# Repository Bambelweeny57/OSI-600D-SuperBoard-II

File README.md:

# Ohio Scientific (OSI) 600D Superboard II Recreation

An open-source hardware recreation of the **Ohio Scientific Superboard II, Model 600 revision D**, the classic 6502 single-board computer, as a complete **KiCad 10** project.

The board keeps the original circuit and copper layout, and adds **Cherry MX keyswitches**, ROM sockets for modern **27C16 EPROMs or 2816 EEPROMs**, pin headers for the option jumpers and a fused power input.

As far as we know, this is the first native KiCad PCB and schematic of the 600D, and the only electronic version of its schematic apart from the original scans.

## Project status

- [x] **Gerber import:** layout converted into KiCad 10 from the reproduction Gerber files by Grant (Klyball).
- [x] **Native KiCad board:** imported copper cleaned up into tracks, vias and footprints; via rings, thin tracks and track ends tidied; mounting holes converted to footprints.
- [x] **Schematic:** five hierarchical sheets following the five OSI pages, with logic drawn as gates. The schematic netlist matches the PCB exactly (269 nets).
- [x] **Verification:** every net checked against the OSI 600 rev D schematic (28 Aug 1980, sheets 1–5), and nets named after the original signal names.
- [x] **DRC:** no violations and no unconnected pads, with the default clearance set to 0.15 mm (the original artwork's spacing).
- [x] **Documentation:** schematic and layout booklet, assembly and test guide, interactive BOM.
- [x] **Schematic wiring:** sheets currently connect by net labels; drawing the wires to match the original pages is in progress.
- [x] **3D model:** Cherry MX switch and keycap models for the 3D view.
- [ ] **First build:** prototype boards to be ordered and tested.

## Repository layout

| Folder | Contents |
|---|---|
| `src/` | KiCad 10 project: top-level schematic, the five sheet files and the PCB |
| `documents/` | Schematic and layout booklet (PDF) and the assembly and test guide (Word) |
| `bom/` | Interactive BOM (`ibom.html`) |
| `images/` | Renders and images used in this README |
| `models/` | 3D models for the KiCad 3D viewer |

## The hardware

| | |
|---|---|
| CPU | MOS 6502 at about 1 MHz (3.93216 MHz crystal) |
| RAM | 8 KB on board in 2114 chips (the original shipped with 4 KB fitted) |
| ROM | Monitor (SYN600) at $F800 and 8 KB Microsoft BASIC at $A000–$BFFF |
| Video | Composite monochrome output, 1 KB video RAM, 2716-type character generator; 32/64 character mode select |
| Keyboard | 53 keys plus Break in the original OSI layout, using Cherry MX switches |
| Storage | Cassette interface; RS-232 serial option through the 6850 ACIA |
| Sound | 8-bit DAC output on J4 |
| Expansion | 40-pin J1 for an OSI 610 board; J75 for the colour option |

## What changed from the original board

- **Cherry MX keyboard:** 54 switch positions. The shift lock can be a Cherry MX Lock switch at SW38 (the original position) or a latching switch at SW54; fit only one.
- **ROMs:** the monitor (U13) and BASIC (U9–U12) sockets take 27C16 or 2816 parts. The character generator (U41) is a 2716-type EPROM.
- **Jumpers:** the original wire-jumper blocks are replaced by pin headers W3 and W5.
- **Power:** 5 V enters at the `+5V_IN` holes and passes through fuse F1 before the protection diode D15.
- **Break key (SW40):** snip off the right-hand plastic peg of the switch; that hole was removed because it cut into the ground strip.
- **Do not fit R88.**

### Reference designators changed for KiCad

KiCad needs every reference to be unique and to end in a number, so these parts were renumbered:

| On the OSI sheets | On this board | Part |
|---|---|---|
| R74 (sheet 1) | R88 | 390 Ω DD pull-down, not fitted |
| R62A (sheet 3) | R90 | 100 Ω cassette input resistor |
| R86 (sheet 5) | R89 | 510 Ω sound DAC pull-up (R86 on sheet 3 keeps its number) |
| D3 LED (sheet 5) | LED1 | Power LED |
| R73 470 Ω (sheet 5) | R87 | LED resistor |
| Shift lock | SW54 or SW38 | Latching shift-lock switch |
| Keys | SW1–SW53 | Cherry MX switches; SW40 is Break |

## Building one

Start with the assembly guide in `documents/`. It follows the order of the 1982 OSI kit manual, with every step rewritten for this board:

1. **Stage I:** sockets, diodes, resistors, capacitors and fittings, with continuity tests.
2. **Stage II:** the Cherry MX keyboard.
3. **Stage III:** a power check with no chips, then the video chips and a picture on screen.
4. **Stage IV:** processor, ROMs and RAM, ending with `7423 BYTES FREE`.

Things to know before you order parts:

- **8T28 bus transceivers** (U24, U25, plus U6, U7 and U74 if you fit the options) are obsolete; use new-old-stock parts. The 8T26 is inverting and will not work.
- **ROMs** need 450 ns or faster parts, programmed with the Superboard II / Challenger 1P images. The character generator needs the OSI 600 character set in 2716 layout.
- **Power supply:** a regulated 5 V supply rated at 3 A.

## Documentation

- **Schematic and layout booklet** (`documents/`): cover, foreword, vector traces of the five original OSI sheets with notes on where this board differs, a component placement drawing, and tables of the reference and net-name changes.
- **Assembly and test guide** (`documents/`): step-by-step build with a location figure for every step, keycap placement table, jumper settings, ROM map, troubleshooting chart and bill of materials.
- **Interactive BOM** (`bom/ibom.html`): open it in a browser to find parts on the board while you build.

## Contributing

Help is welcome, especially with:

1. **Schematic wiring:** drawing the wires on the five sheets to match the original pages. The booklet's traced sheets are the reference.
2. **Testing:** building a board and reporting results.
3. **3D models:** Cherry MX switch and keycap models with legends.

Please open an issue or a pull request.

## Credits

- **Ohio Scientific Instruments:** for the original Superboard II and its documentation.
- **Grant (Klyball):** for the reproduction Gerber files this layout is built on.
- **Jon (Bambelweeny57), Submeson Brain Corporation:** KiCad conversion, Cherry MX edition and documentation.

## Licence

This project is shared for educational and preservation purposes. The original Ohio Scientific schematics and manuals remain subject to their original copyrights.

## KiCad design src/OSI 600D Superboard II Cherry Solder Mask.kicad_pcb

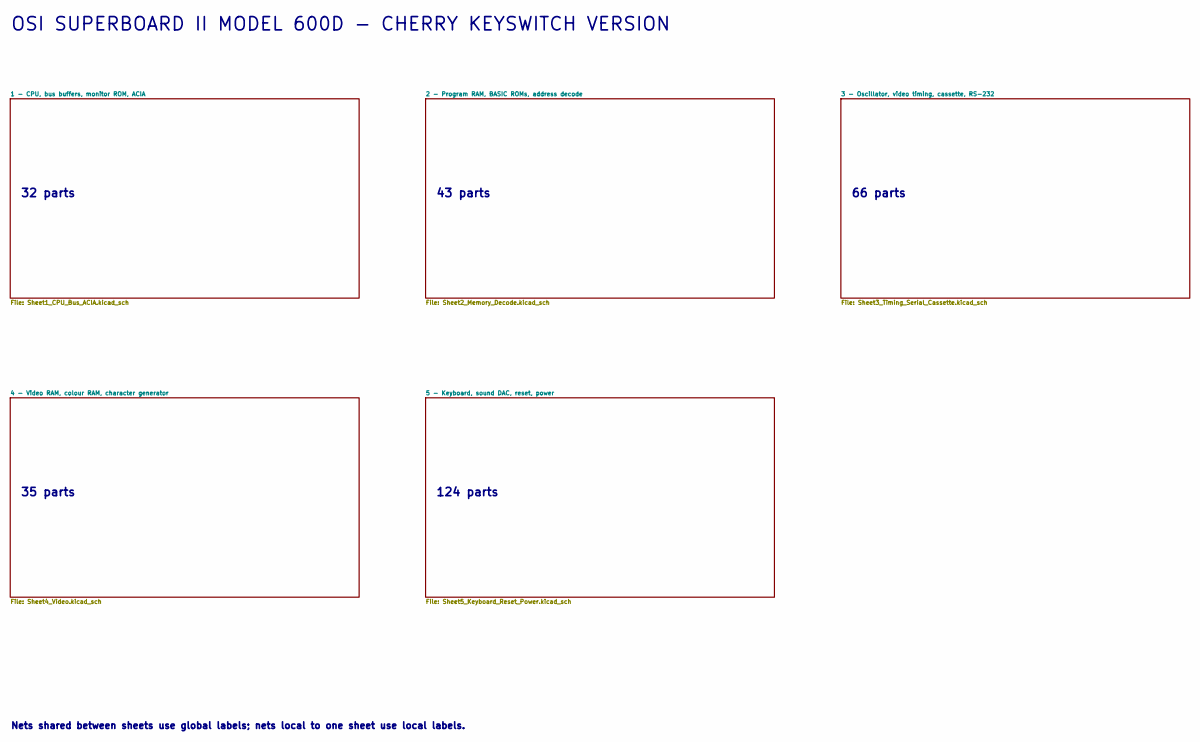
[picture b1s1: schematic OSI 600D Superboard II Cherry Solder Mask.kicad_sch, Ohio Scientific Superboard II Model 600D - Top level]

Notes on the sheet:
32 parts
43 parts
Nets shared between sheets use global labels; nets local to one sheet use local labels.
35 parts
OSI SUPERBOARD II MODEL 600D - CHERRY KEYSWITCH VERSION
124 parts
66 parts

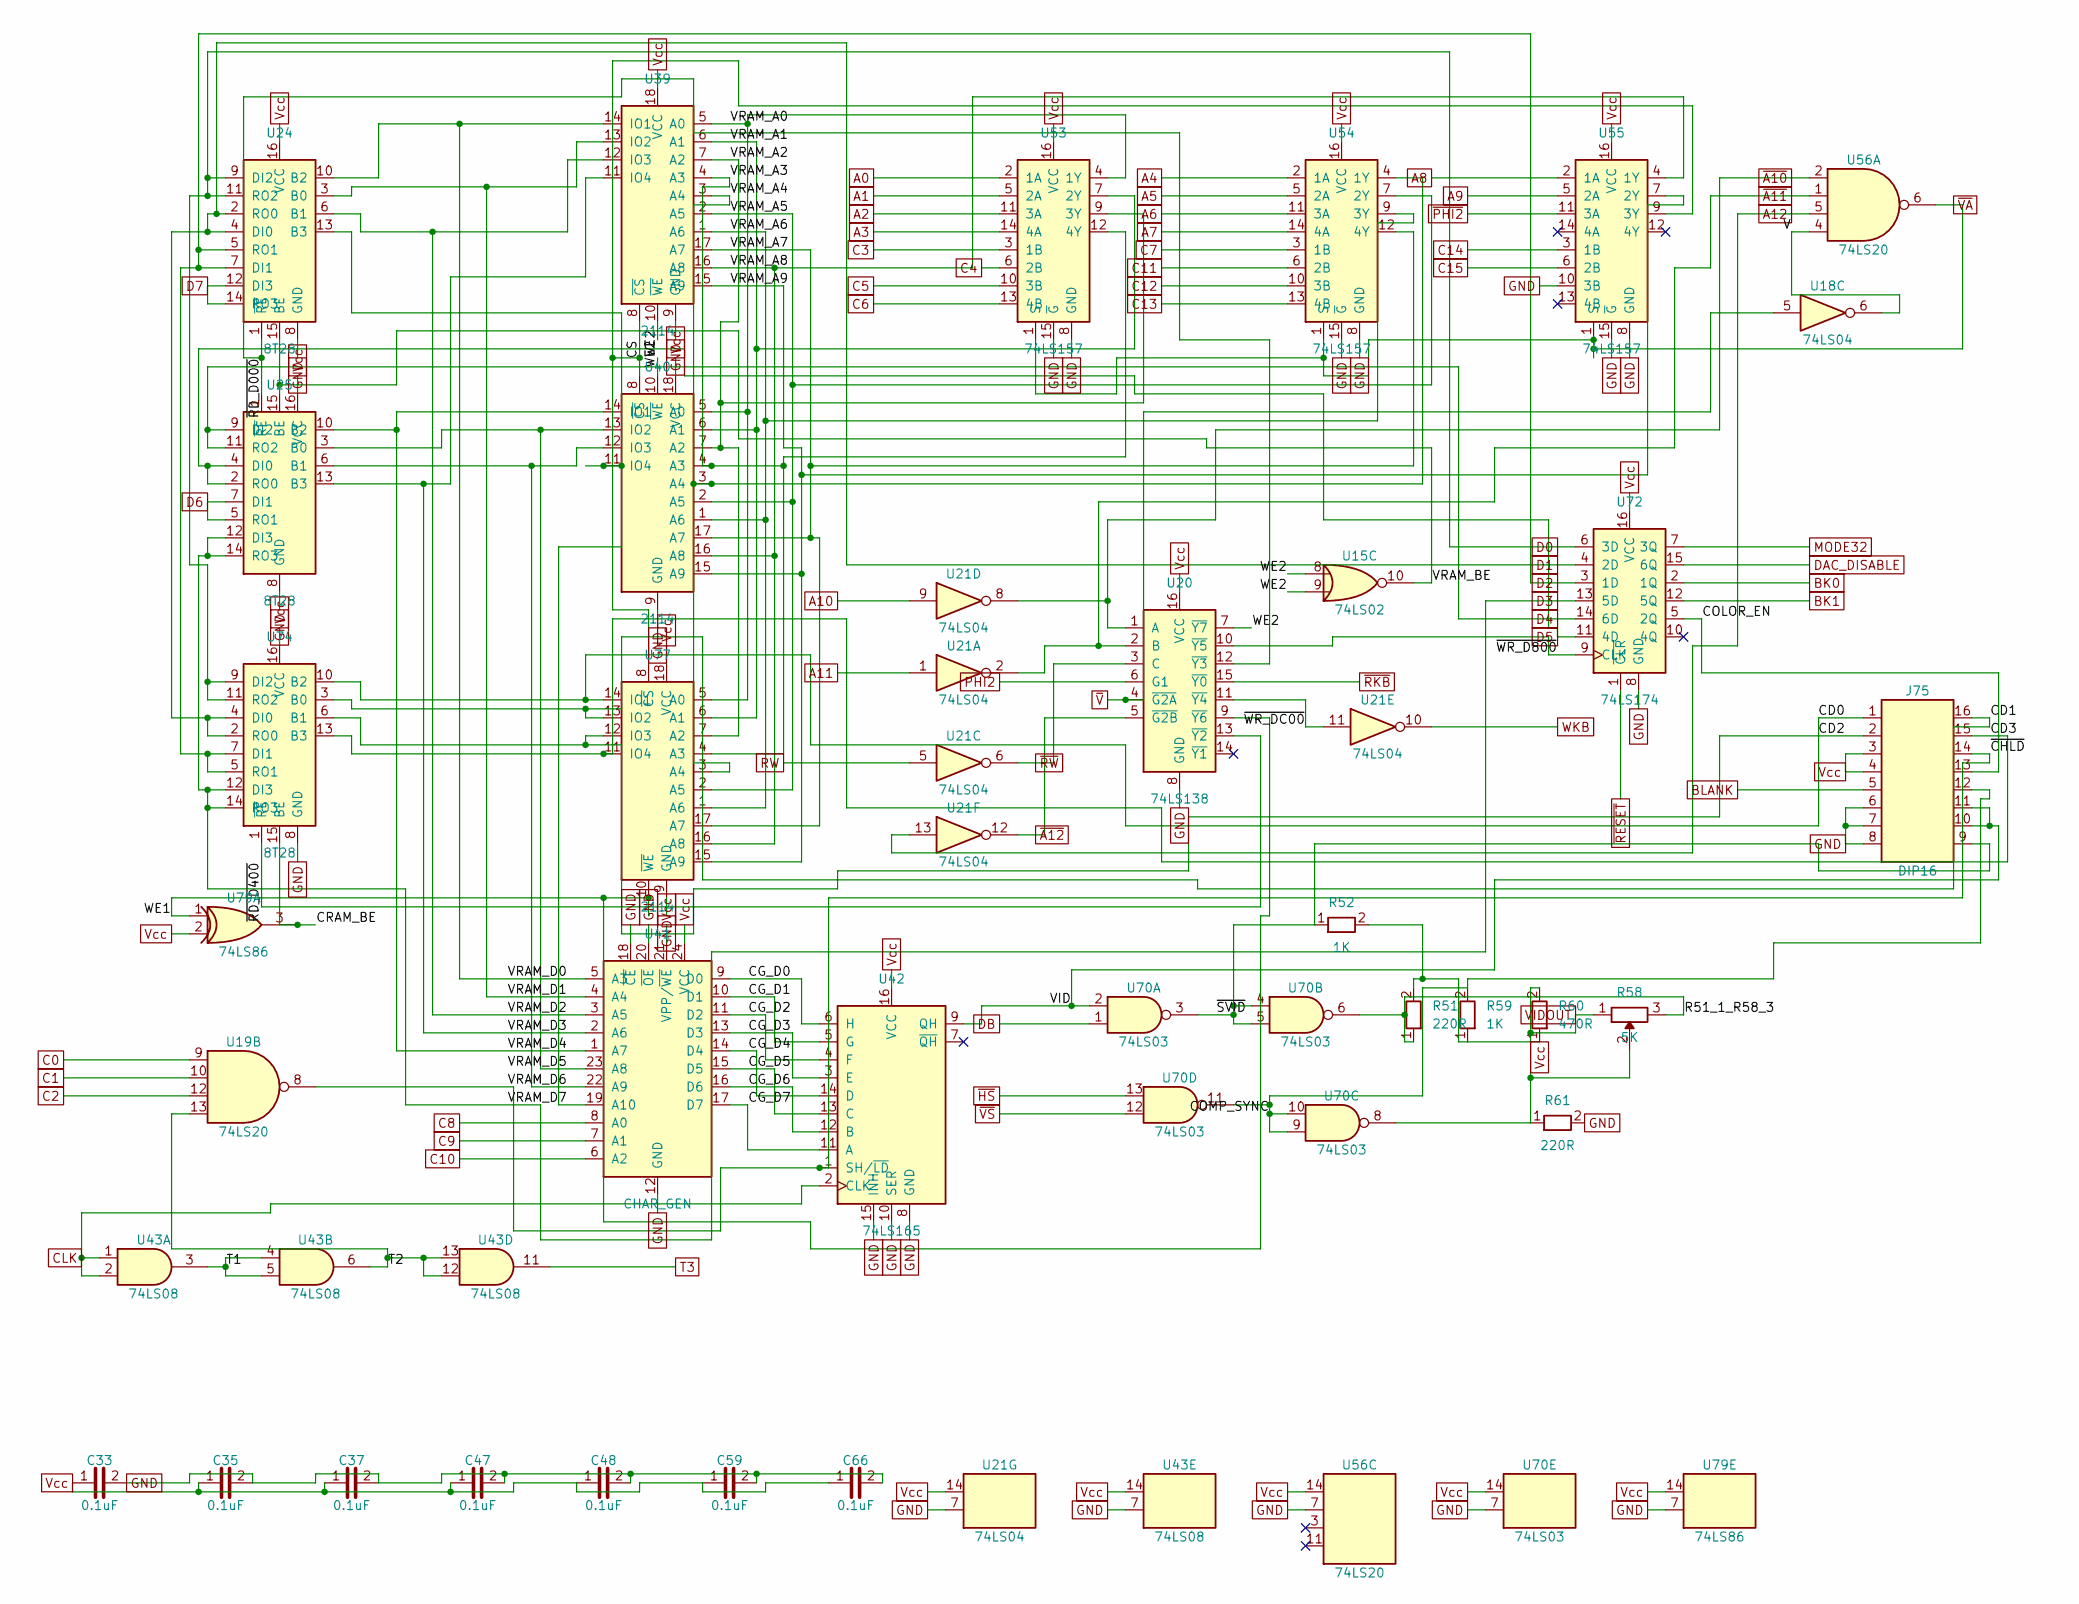
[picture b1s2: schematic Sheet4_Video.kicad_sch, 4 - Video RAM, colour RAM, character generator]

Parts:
C33, C35, C37, C47, C48, C59, C66: 0.1uF; C_Rect_L10.0mm_W3.0mm_P7.50mm_FKS3_FKP3
J75: DIP16; DIP-16_W7.62mm_LongPads
R51, R61: 220R; R_Axial_DIN0207_L6.3mm_D2.5mm_P2.54mm_Vertical
R52, R59: 1K; R_Axial_DIN0207_L6.3mm_D2.5mm_P2.54mm_Vertical
R58: 5K; Potentiometer_Bourns_3266Y_Vertical
R60: 470R; R_Axial_DIN0207_L6.3mm_D2.5mm_P2.54mm_Vertical
U15: 74LS02; DIP-14_W7.62mm_LongPads
U18, U21: 74LS04; DIP-14_W7.62mm_LongPads
U19, U56: 74LS20; DIP-14_W7.62mm_LongPads
U20: 74LS138; DIP-16_W7.62mm_LongPads
U24, U25, U74: 8T28; DIP-16_W7.62mm_LongPads
U39, U40, U77: 2114; DIP-18_W7.62mm_LongPads
U41: CHAR_GEN; DIP-24_W15.24mm_LongPads
U42: 74LS165; DIP-16_W7.62mm_LongPads
U43: 74LS08; DIP-14_W7.62mm_LongPads
U53, U54, U55: 74LS157; DIP-16_W7.62mm_LongPads
U70: 74LS03; DIP-14_W7.62mm_LongPads
U72: 74LS174; DIP-16_W7.62mm_LongPads
U79: 74LS86; DIP-14_W7.62mm_LongPads

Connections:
A0: U53.2 (1A); also elsewhere on the board
A1: U53.5 (2A); also elsewhere on the board
A2: U53.11 (3A); also elsewhere on the board
A3: U53.14 (4A); also elsewhere on the board
A4: U54.2 (1A); also elsewhere on the board
A5: U54.5 (2A); also elsewhere on the board
A6: U54.11 (3A); also elsewhere on the board
A7: U54.14 (4A); also elsewhere on the board
A8: U55.2 (1A); also elsewhere on the board
A9: U55.5 (2A); also elsewhere on the board
A10: U21.9; also elsewhere on the board
A11: U21.1; also elsewhere on the board
A12: U21.13, U56.5; also elsewhere on the board
BK0: U72.2 (1Q); also elsewhere on the board
BK1: U72.12 (5Q); also elsewhere on the board
BLANK: J75.5; also elsewhere on the board
C0: U19.9; also elsewhere on the board
C1: U19.10; also elsewhere on the board
C2: U19.12; also elsewhere on the board
C3: U53.3 (1B); also elsewhere on the board
C4: U53.6 (2B); also elsewhere on the board
C5: U53.10 (3B); also elsewhere on the board
C6: U53.13 (4B); also elsewhere on the board
C7: U54.3 (1B); also elsewhere on the board
C8: U41.8 (A0); also elsewhere on the board
C9: U41.7 (A1); also elsewhere on the board
C10: U41.6 (A2); also elsewhere on the board
C11: U54.6 (2B); also elsewhere on the board
C12: U54.10 (3B); also elsewhere on the board
C13: U54.13 (4B); also elsewhere on the board
C14: U55.3 (1B); also elsewhere on the board
C15: U55.6 (2B); also elsewhere on the board
CD0: J75.1, U74.10 (B2), U77.14 (IO1)
CD1: J75.16, U74.3 (B0), U77.13 (IO2)
CD2: J75.2, U74.6 (B1), U77.12 (IO3)
CD3: J75.15, U74.13 (B3), U77.11 (IO4)
CG_D0: U41.9 (D0), U42.6 (H)
CG_D1: U41.10 (D1), U42.5 (G)
CG_D2: U41.11 (D2), U42.4 (F)
CG_D3: U41.13 (D3), U42.3 (E)
CG_D4: U41.14 (D4), U42.14 (D)
CG_D5: U41.15 (D5), U42.13 (C)
CG_D6: U41.16 (D6), U42.12 (B)
CG_D7: U41.17 (D7), U42.11 (A)
CLK: U42.2 (CLK), U43.1, U43.2; also elsewhere on the board
COLOR_EN: J75.13, U72.5 (2Q)
COMP_SYNC: J75.12, R59.2, U70.9, U70.10, U70.11
CRAM_BE: U74.15 (BE), U79.3
CS: U39.8 (~CS), U40.8 (~CS), U55.9 (3Y), U77.8 (~CS)
D0: U24.9 (DI2), U24.11 (RO2), U72.6 (3D), U74.9 (DI2), U74.11 (RO2); also elsewhere on the board
D1: U24.2 (RO0), U24.4 (DI0), U72.4 (2D), U74.2 (RO0), U74.4 (DI0); also elsewhere on the board
D2: U24.5 (RO1), U24.7 (DI1), U72.3 (1D), U74.5 (RO1), U74.7 (DI1); also elsewhere on the board
D3: U25.12 (DI3), U25.14 (RO3), U72.13 (5D), U74.12 (DI3), U74.14 (RO3); also elsewhere on the board
D4: U25.9 (DI2), U25.11 (RO2), U72.14 (6D); also elsewhere on the board
D5: U25.2 (RO0), U25.4 (DI0), U72.11 (4D); also elsewhere on the board
D6: U25.5 (RO1), U25.7 (DI1); also elsewhere on the board
D7: U24.12 (DI3), U24.14 (RO3); also elsewhere on the board
DAC_DISABLE: U72.15 (6Q); also elsewhere on the board
DB: U70.1; also elsewhere on the board
GND: C33.2, C35.2, C37.2, C47.2, C48.2, C59.2, C66.2, J75.6, J75.7, J75.8, R61.2, U20.8 (GND), U21.7 (GND), U24.8 (GND), U25.8 (GND), U39.9 (GND), U40.9 (GND), U41.12 (GND), U41.18 (~CE), U41.20 (~OE), U42.8 (GND), U42.10 (SER), U42.15 (INH), U43.7 (GND), U53.8 (GND), U53.15 (~G), U54.8 (GND), U54.15 (~G), U55.8 (GND), U55.10 (3B), U55.15 (~G), U56.7 (GND), U70.7 (GND), U72.8 (GND), U74.8 (GND), U77.9 (GND), U79.7 (GND); also elsewhere on the board
MODE32: U72.7 (3Q); also elsewhere on the board
PHI2: U20.6 (G1); also elsewhere on the board
R51_1_R58_3: R51.1, R58.3, U70.6
RW: U21.5; also elsewhere on the board
T1: U43.3, U43.4, U43.5
T2: U19.13, U43.6, U43.12, U43.13
T3: U43.11; also elsewhere on the board
V: U18.6, U56.4
VID: J75.10, J75.11, U42.9 (QH), U70.2
VIDOUT: R58.1, R58.2, R60.2, R61.1, U70.8; also elsewhere on the board
VRAM_A0: U39.5 (A0), U40.5 (A0), U53.4 (1Y), U77.5 (A0)
VRAM_A1: U39.6 (A1), U40.6 (A1), U53.7 (2Y), U77.6 (A1)
VRAM_A2: U39.7 (A2), U40.7 (A2), U53.9 (3Y), U77.7 (A2)
VRAM_A3: U39.4 (A3), U40.4 (A3), U53.12 (4Y), U77.4 (A3)
VRAM_A4: U39.3 (A4), U40.3 (A4), U54.4 (1Y), U77.3 (A4)
VRAM_A5: U39.2 (A5), U40.2 (A5), U54.7 (2Y), U77.2 (A5)
VRAM_A6: U39.1 (A6), U40.1 (A6), U54.9 (3Y), U77.1 (A6)
VRAM_A7: U39.17 (A7), U40.17 (A7), U54.12 (4Y), U77.17 (A7)
VRAM_A8: U39.16 (A8), U40.16 (A8), U55.4 (1Y), U77.16 (A8)
VRAM_A9: U39.15 (A9), U40.15 (A9), U55.7 (2Y), U77.15 (A9)
VRAM_BE: U15.10, U24.15 (BE), U25.15 (BE)
VRAM_D0: U24.10 (B2), U39.14 (IO1), U41.5 (A3)
VRAM_D1: U24.3 (B0), U39.13 (IO2), U41.4 (A4)
VRAM_D2: U24.6 (B1), U39.12 (IO3), U41.3 (A5)
VRAM_D3: U25.13 (B3), U39.11 (IO4), U41.2 (A6)
VRAM_D4: U25.10 (B2), U40.14 (IO1), U41.1 (A7)
VRAM_D5: U25.3 (B0), U40.13 (IO2), U41.23 (A8)
VRAM_D6: U25.6 (B1), U40.12 (IO3), U41.22 (A9)
VRAM_D7: U24.13 (B3), U40.11 (IO4), U41.19 (A10)
Vcc: C33.1, C35.1, C37.1, C47.1, C48.1, C59.1, C66.1, J75.3, J75.4, R51.2, R52.2, R59.1, R60.1, U20.16 (VCC), U21.14 (VCC), U24.16 (VCC), U25.16 (VCC), U39.18 (VCC), U40.18 (VCC), U41.21 (VPP/~WE), U41.24 (VCC), U42.16 (VCC), U43.14 (VCC), U53.16 (VCC), U54.16 (VCC), U55.16 (VCC), U56.14 (VCC), U70.14 (VCC), U72.16 (VCC), U74.16 (VCC), U77.18 (VCC), U79.2, U79.14 (VCC); also elsewhere on the board
WE1: U20.9 (~Y6), U77.10 (~WE), U79.1
WE2: U15.8, U15.9, U20.7 (~Y7), U39.10 (~WE), U40.10 (~WE)
WKB: U21.10; also elsewhere on the board
~A10: U20.1 (A), U21.8, U56.2; also elsewhere on the board
~A11: U20.2 (B), U21.2, U56.1; also elsewhere on the board
~A12: U20.5 (~G2B), U21.12; also elsewhere on the board
~CHLD: J75.14, U19.8, U42.1 (SH/~LD)
~HS: U70.13; also elsewhere on the board
~PHI2: U55.11 (3A); also elsewhere on the board
~RD_D000: U20.12 (~Y3), U24.1 (~RE), U25.1 (~RE)
~RD_D400: U20.13 (~Y2), U74.1 (~RE)
~RESET: U72.1 (~CLR); also elsewhere on the board
~RKB: U20.15 (~Y0); also elsewhere on the board
~RW: U20.3 (C), U21.6; also elsewhere on the board
~SVID: J75.9, R52.1, U70.3, U70.4, U70.5
~VA: U53.1 (S), U54.1 (S), U55.1 (S), U56.6; also elsewhere on the board
~VS: U70.12; also elsewhere on the board
~V: U18.5, U20.4 (~G2A); also elsewhere on the board
~WR_D800: U20.10 (~Y5), U72.9 (CLK)
~WR_DC00: U20.11 (~Y4), U21.11

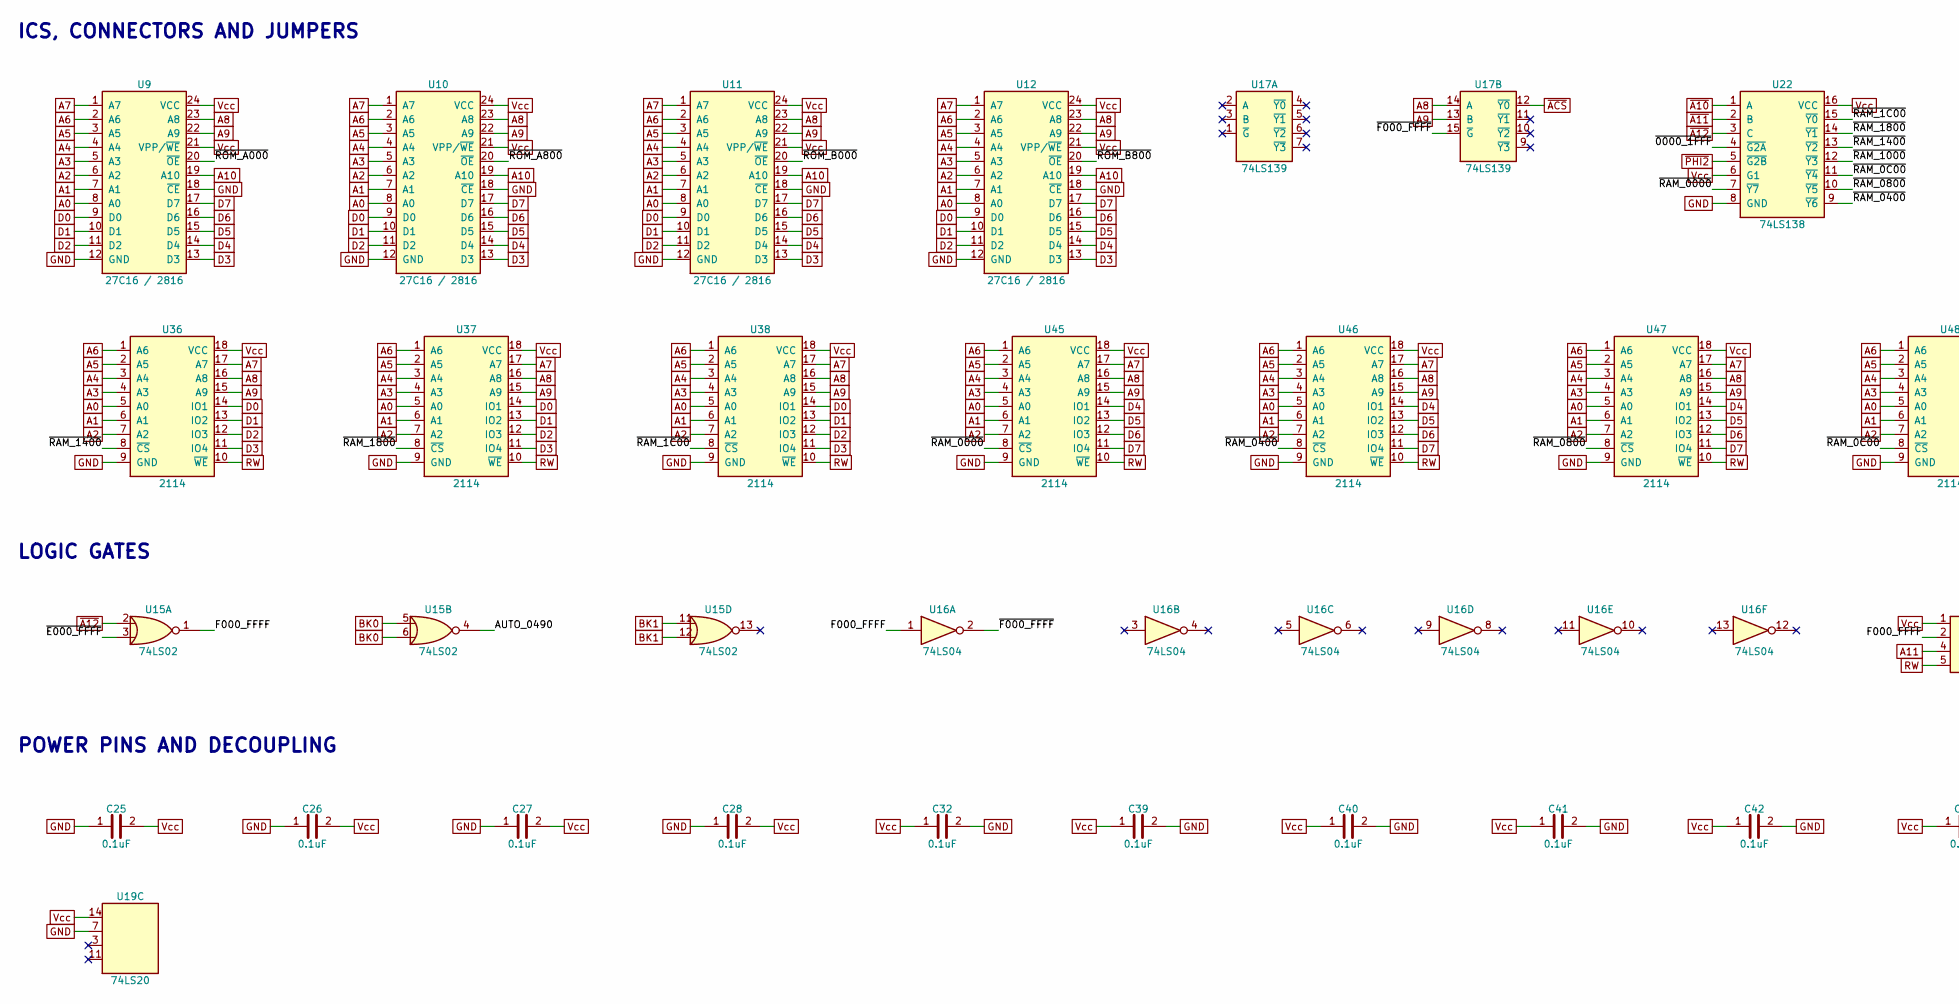
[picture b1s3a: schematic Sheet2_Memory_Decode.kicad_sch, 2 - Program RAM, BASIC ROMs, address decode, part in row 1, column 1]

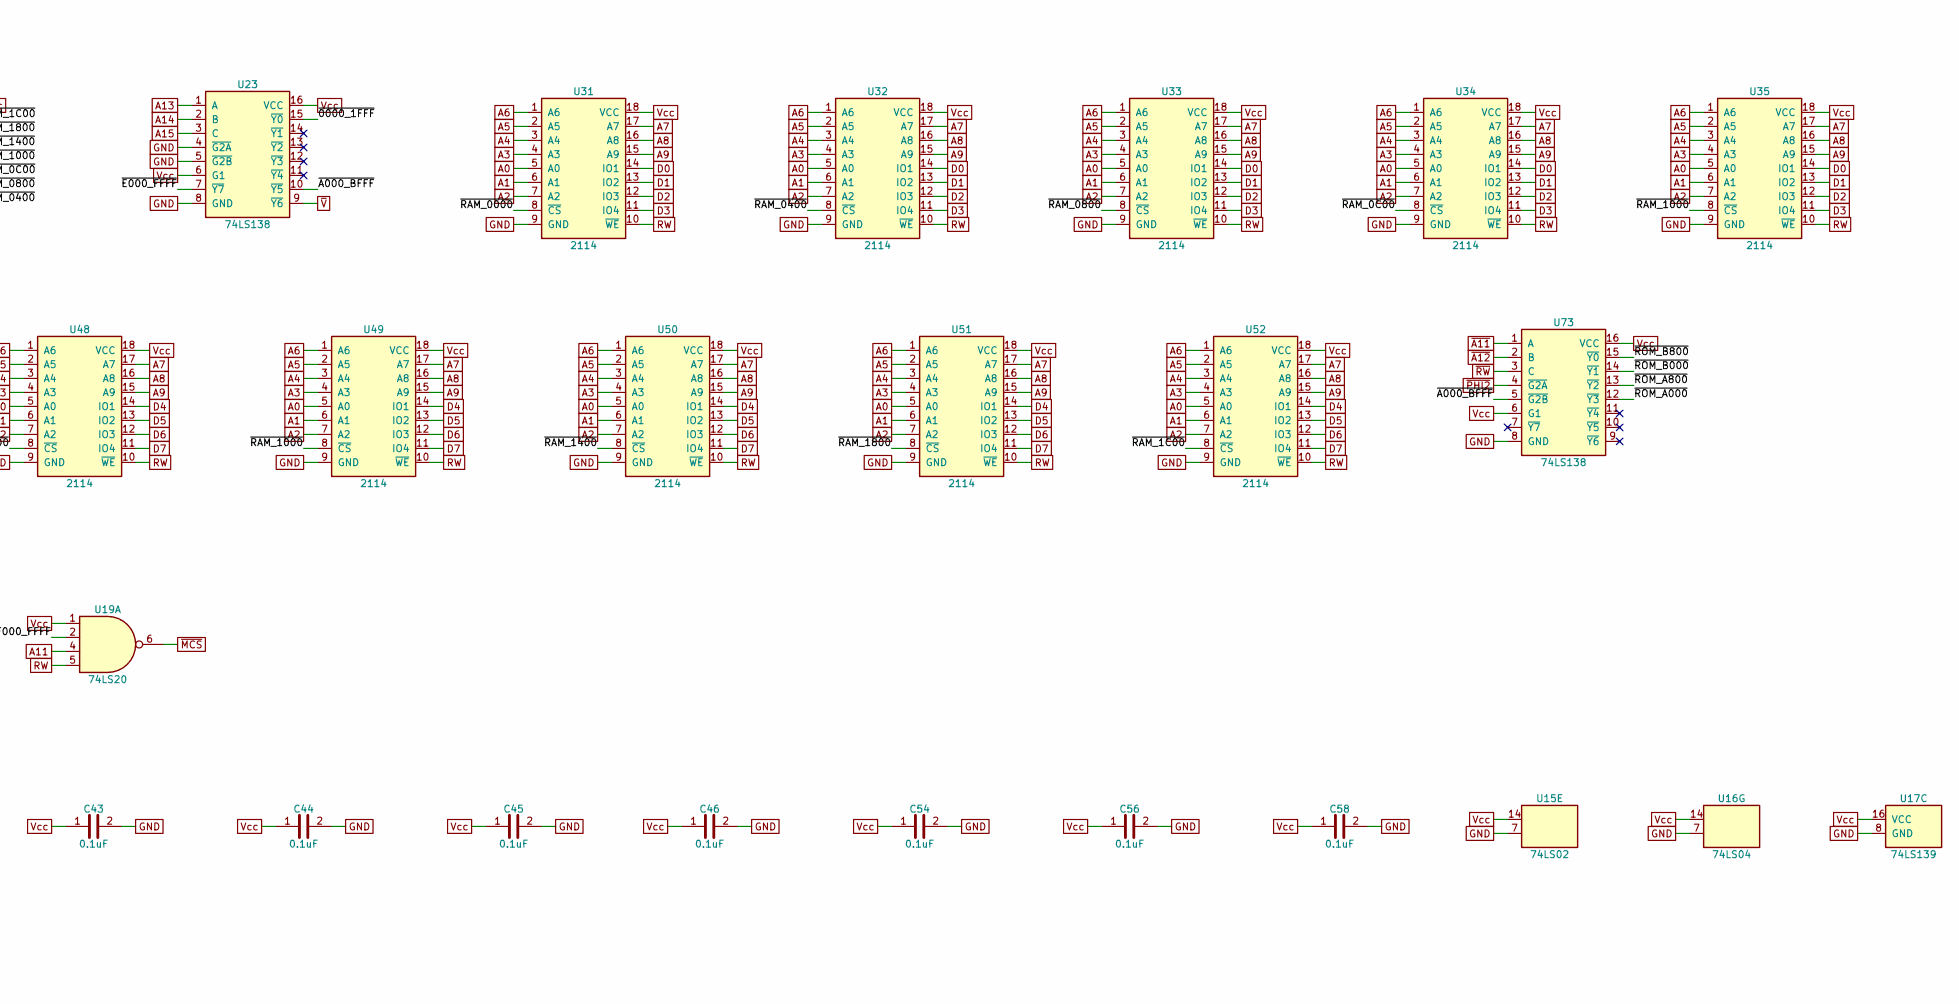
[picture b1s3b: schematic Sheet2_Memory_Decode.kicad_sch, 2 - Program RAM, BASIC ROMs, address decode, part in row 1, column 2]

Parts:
C25, C26, C27, C28, C32, C39, C40, C41, C42, C43, C44, C45, C46, C54, C56, C58: 0.1uF; C_Rect_L10.0mm_W3.0mm_P7.50mm_FKS3_FKP3
U9, U10, U11, U12: 27C16 / 2816; DIP-24_W15.24mm_LongPads
U15: 74LS02; DIP-14_W7.62mm_LongPads
U16: 74LS04; DIP-14_W7.62mm_LongPads
U17: 74LS139; DIP-16_W7.62mm_LongPads
U19: 74LS20; DIP-14_W7.62mm_LongPads
U22, U23, U73: 74LS138; DIP-16_W7.62mm_LongPads
U31, U32, U33, U34, U35, U36, U37, U38, U45, U46, U47, U48, U49, U50, U51, U52: 2114; DIP-18_W7.62mm_LongPads

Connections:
A0: U9.8 (A0), U10.8 (A0), U11.8 (A0), U12.8 (A0), U31.5 (A0), U32.5 (A0), U33.5 (A0), U34.5 (A0), U35.5 (A0), U36.5 (A0), U37.5 (A0), U38.5 (A0), U45.5 (A0), U46.5 (A0), U47.5 (A0), U48.5 (A0), U49.5 (A0), U50.5 (A0), U51.5 (A0), U52.5 (A0); also elsewhere on the board
A1: U9.7 (A1), U10.7 (A1), U11.7 (A1), U12.7 (A1), U31.6 (A1), U32.6 (A1), U33.6 (A1), U34.6 (A1), U35.6 (A1), U36.6 (A1), U37.6 (A1), U38.6 (A1), U45.6 (A1), U46.6 (A1), U47.6 (A1), U48.6 (A1), U49.6 (A1), U50.6 (A1), U51.6 (A1), U52.6 (A1); also elsewhere on the board
A2: U9.6 (A2), U10.6 (A2), U11.6 (A2), U12.6 (A2), U31.7 (A2), U32.7 (A2), U33.7 (A2), U34.7 (A2), U35.7 (A2), U36.7 (A2), U37.7 (A2), U38.7 (A2), U45.7 (A2), U46.7 (A2), U47.7 (A2), U48.7 (A2), U49.7 (A2), U50.7 (A2), U51.7 (A2), U52.7 (A2); also elsewhere on the board
A3: U9.5 (A3), U10.5 (A3), U11.5 (A3), U12.5 (A3), U31.4 (A3), U32.4 (A3), U33.4 (A3), U34.4 (A3), U35.4 (A3), U36.4 (A3), U37.4 (A3), U38.4 (A3), U45.4 (A3), U46.4 (A3), U47.4 (A3), U48.4 (A3), U49.4 (A3), U50.4 (A3), U51.4 (A3), U52.4 (A3); also elsewhere on the board
A4: U9.4 (A4), U10.4 (A4), U11.4 (A4), U12.4 (A4), U31.3 (A4), U32.3 (A4), U33.3 (A4), U34.3 (A4), U35.3 (A4), U36.3 (A4), U37.3 (A4), U38.3 (A4), U45.3 (A4), U46.3 (A4), U47.3 (A4), U48.3 (A4), U49.3 (A4), U50.3 (A4), U51.3 (A4), U52.3 (A4); also elsewhere on the board
A5: U9.3 (A5), U10.3 (A5), U11.3 (A5), U12.3 (A5), U31.2 (A5), U32.2 (A5), U33.2 (A5), U34.2 (A5), U35.2 (A5), U36.2 (A5), U37.2 (A5), U38.2 (A5), U45.2 (A5), U46.2 (A5), U47.2 (A5), U48.2 (A5), U49.2 (A5), U50.2 (A5), U51.2 (A5), U52.2 (A5); also elsewhere on the board
A6: U9.2 (A6), U10.2 (A6), U11.2 (A6), U12.2 (A6), U31.1 (A6), U32.1 (A6), U33.1 (A6), U34.1 (A6), U35.1 (A6), U36.1 (A6), U37.1 (A6), U38.1 (A6), U45.1 (A6), U46.1 (A6), U47.1 (A6), U48.1 (A6), U49.1 (A6), U50.1 (A6), U51.1 (A6), U52.1 (A6); also elsewhere on the board
A7: U9.1 (A7), U10.1 (A7), U11.1 (A7), U12.1 (A7), U31.17 (A7), U32.17 (A7), U33.17 (A7), U34.17 (A7), U35.17 (A7), U36.17 (A7), U37.17 (A7), U38.17 (A7), U45.17 (A7), U46.17 (A7), U47.17 (A7), U48.17 (A7), U49.17 (A7), U50.17 (A7), U51.17 (A7), U52.17 (A7); also elsewhere on the board
A8: U9.23 (A8), U10.23 (A8), U11.23 (A8), U12.23 (A8), U17.14 (A), U31.16 (A8), U32.16 (A8), U33.16 (A8), U34.16 (A8), U35.16 (A8), U36.16 (A8), U37.16 (A8), U38.16 (A8), U45.16 (A8), U46.16 (A8), U47.16 (A8), U48.16 (A8), U49.16 (A8), U50.16 (A8), U51.16 (A8), U52.16 (A8); also elsewhere on the board
A9: U9.22 (A9), U10.22 (A9), U11.22 (A9), U12.22 (A9), U17.13 (B), U31.15 (A9), U32.15 (A9), U33.15 (A9), U34.15 (A9), U35.15 (A9), U36.15 (A9), U37.15 (A9), U38.15 (A9), U45.15 (A9), U46.15 (A9), U47.15 (A9), U48.15 (A9), U49.15 (A9), U50.15 (A9), U51.15 (A9), U52.15 (A9); also elsewhere on the board
A10: U9.19 (A10), U10.19 (A10), U11.19 (A10), U12.19 (A10); also elsewhere on the board
A11: U19.4; also elsewhere on the board
A13: U23.1 (A); also elsewhere on the board
A14: U23.2 (B); also elsewhere on the board
A15: U23.3 (C); also elsewhere on the board
AUTO_0490: U15.4
BK0: U15.5, U15.6; also elsewhere on the board
BK1: U15.11, U15.12; also elsewhere on the board
D0: U9.9 (D0), U10.9 (D0), U11.9 (D0), U12.9 (D0), U31.14 (IO1), U32.14 (IO1), U33.14 (IO1), U34.14 (IO1), U35.14 (IO1), U36.14 (IO1), U37.14 (IO1), U38.14 (IO1); also elsewhere on the board
D1: U9.10 (D1), U10.10 (D1), U11.10 (D1), U12.10 (D1), U31.13 (IO2), U32.13 (IO2), U33.13 (IO2), U34.13 (IO2), U35.13 (IO2), U36.13 (IO2), U37.13 (IO2), U38.13 (IO2); also elsewhere on the board
D2: U9.11 (D2), U10.11 (D2), U11.11 (D2), U12.11 (D2), U31.12 (IO3), U32.12 (IO3), U33.12 (IO3), U34.12 (IO3), U35.12 (IO3), U36.12 (IO3), U37.12 (IO3), U38.12 (IO3); also elsewhere on the board
D3: U9.13 (D3), U10.13 (D3), U11.13 (D3), U12.13 (D3), U31.11 (IO4), U32.11 (IO4), U33.11 (IO4), U34.11 (IO4), U35.11 (IO4), U36.11 (IO4), U37.11 (IO4), U38.11 (IO4); also elsewhere on the board
D4: U9.14 (D4), U10.14 (D4), U11.14 (D4), U12.14 (D4), U45.14 (IO1), U46.14 (IO1), U47.14 (IO1), U48.14 (IO1), U49.14 (IO1), U50.14 (IO1), U51.14 (IO1), U52.14 (IO1); also elsewhere on the board
D5: U9.15 (D5), U10.15 (D5), U11.15 (D5), U12.15 (D5), U45.13 (IO2), U46.13 (IO2), U47.13 (IO2), U48.13 (IO2), U49.13 (IO2), U50.13 (IO2), U51.13 (IO2), U52.13 (IO2); also elsewhere on the board
D6: U9.16 (D6), U10.16 (D6), U11.16 (D6), U12.16 (D6), U45.12 (IO3), U46.12 (IO3), U47.12 (IO3), U48.12 (IO3), U49.12 (IO3), U50.12 (IO3), U51.12 (IO3), U52.12 (IO3); also elsewhere on the board
D7: U9.17 (D7), U10.17 (D7), U11.17 (D7), U12.17 (D7), U45.11 (IO4), U46.11 (IO4), U47.11 (IO4), U48.11 (IO4), U49.11 (IO4), U50.11 (IO4), U51.11 (IO4), U52.11 (IO4); also elsewhere on the board
F000_FFFF: U15.1, U16.1, U19.2
GND: C25.1, C26.1, C27.1, C28.1, C32.2, C39.2, C40.2, C41.2, C42.2, C43.2, C44.2, C45.2, C46.2, C54.2, C56.2, C58.2, U9.12 (GND), U9.18 (~CE), U10.12 (GND), U10.18 (~CE), U11.12 (GND), U11.18 (~CE), U12.12 (GND), U12.18 (~CE), U15.7 (GND), U16.7 (GND), U17.8 (GND), U19.7 (GND), U22.8 (GND), U23.4 (~G2A), U23.5 (~G2B), U23.8 (GND), U31.9 (GND), U32.9 (GND), U33.9 (GND), U34.9 (GND), U35.9 (GND), U36.9 (GND), U37.9 (GND), U38.9 (GND), U45.9 (GND), U46.9 (GND), U47.9 (GND), U48.9 (GND), U49.9 (GND), U50.9 (GND), U51.9 (GND), U52.9 (GND), U73.8 (GND); also elsewhere on the board
RW: U19.5, U31.10 (~WE), U32.10 (~WE), U33.10 (~WE), U34.10 (~WE), U35.10 (~WE), U36.10 (~WE), U37.10 (~WE), U38.10 (~WE), U45.10 (~WE), U46.10 (~WE), U47.10 (~WE), U48.10 (~WE), U49.10 (~WE), U50.10 (~WE), U51.10 (~WE), U52.10 (~WE); also elsewhere on the board
Vcc: C25.2, C26.2, C27.2, C28.2, C32.1, C39.1, C40.1, C41.1, C42.1, C43.1, C44.1, C45.1, C46.1, C54.1, C56.1, C58.1, U9.21 (VPP/~WE), U9.24 (VCC), U10.21 (VPP/~WE), U10.24 (VCC), U11.21 (VPP/~WE), U11.24 (VCC), U12.21 (VPP/~WE), U12.24 (VCC), U15.14 (VCC), U16.14 (VCC), U17.16 (VCC), U19.1, U19.14 (VCC), U22.6 (G1), U22.16 (VCC), U23.6 (G1), U23.16 (VCC), U31.18 (VCC), U32.18 (VCC), U33.18 (VCC), U34.18 (VCC), U35.18 (VCC), U36.18 (VCC), U37.18 (VCC), U38.18 (VCC), U45.18 (VCC), U46.18 (VCC), U47.18 (VCC), U48.18 (VCC), U49.18 (VCC), U50.18 (VCC), U51.18 (VCC), U52.18 (VCC), U73.6 (G1), U73.16 (VCC); also elsewhere on the board
~0000_1FFF: U22.4 (~G2A), U23.15 (~Y0)
~A000_BFFF: U23.10 (~Y5), U73.5 (~G2B)
~A10: U22.1 (A); also elsewhere on the board
~A11: U22.2 (B), U73.1 (A); also elsewhere on the board
~A12: U15.2, U22.3 (C), U73.2 (B); also elsewhere on the board
~ACS: U17.12 (~Y0); also elsewhere on the board
~E000_FFFF: U15.3, U23.7 (~Y7)
~F000_FFFF: U16.2, U17.15 (~G)
~MCS: U19.6; also elsewhere on the board
~PHI2: U22.5 (~G2B), U73.4 (~G2A); also elsewhere on the board
~RAM_0C00: U22.11 (~Y4), U34.8 (~CS), U48.8 (~CS)
~RAM_0000: U22.7 (~Y7), U31.8 (~CS), U45.8 (~CS)
~RAM_1C00: U22.15 (~Y0), U38.8 (~CS), U52.8 (~CS)
~RAM_0400: U22.9 (~Y6), U32.8 (~CS), U46.8 (~CS)
~RAM_0800: U22.10 (~Y5), U33.8 (~CS), U47.8 (~CS)
~RAM_1000: U22.12 (~Y3), U35.8 (~CS), U49.8 (~CS)
~RAM_1400: U22.13 (~Y2), U36.8 (~CS), U50.8 (~CS)
~RAM_1800: U22.14 (~Y1), U37.8 (~CS), U51.8 (~CS)
~ROM_A000: U9.20 (~OE), U73.12 (~Y3)
~ROM_A800: U10.20 (~OE), U73.13 (~Y2)
~ROM_B000: U11.20 (~OE), U73.14 (~Y1)
~ROM_B800: U12.20 (~OE), U73.15 (~Y0)
~RW: U73.3 (C); also elsewhere on the board
~V: U23.9 (~Y6); also elsewhere on the board

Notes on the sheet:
ICS, CONNECTORS AND JUMPERS
LOGIC GATES
POWER PINS AND DECOUPLING
